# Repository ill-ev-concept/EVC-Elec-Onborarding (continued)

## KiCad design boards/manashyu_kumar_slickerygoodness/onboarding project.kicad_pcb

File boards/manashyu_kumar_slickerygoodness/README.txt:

Lights controller onboarding project
Manashyu Kumar

Open onboarding project.kicad_pro in KiCad 10.
Two-layer board, 85 x 65 mm.

Backpack.pretty and libs contain the custom footprints and symbols.
manufacturing contains the Gerber and separate plated/nonplated drill files.

DRC and schematic parity checks passed on October 12, 2026 using the project's configured rules.
For team review: confirm connector pinouts and fit, LED load current, and power-track capacity before fabrication. CAN and main grounds are separate; isolation performance has not been validated.

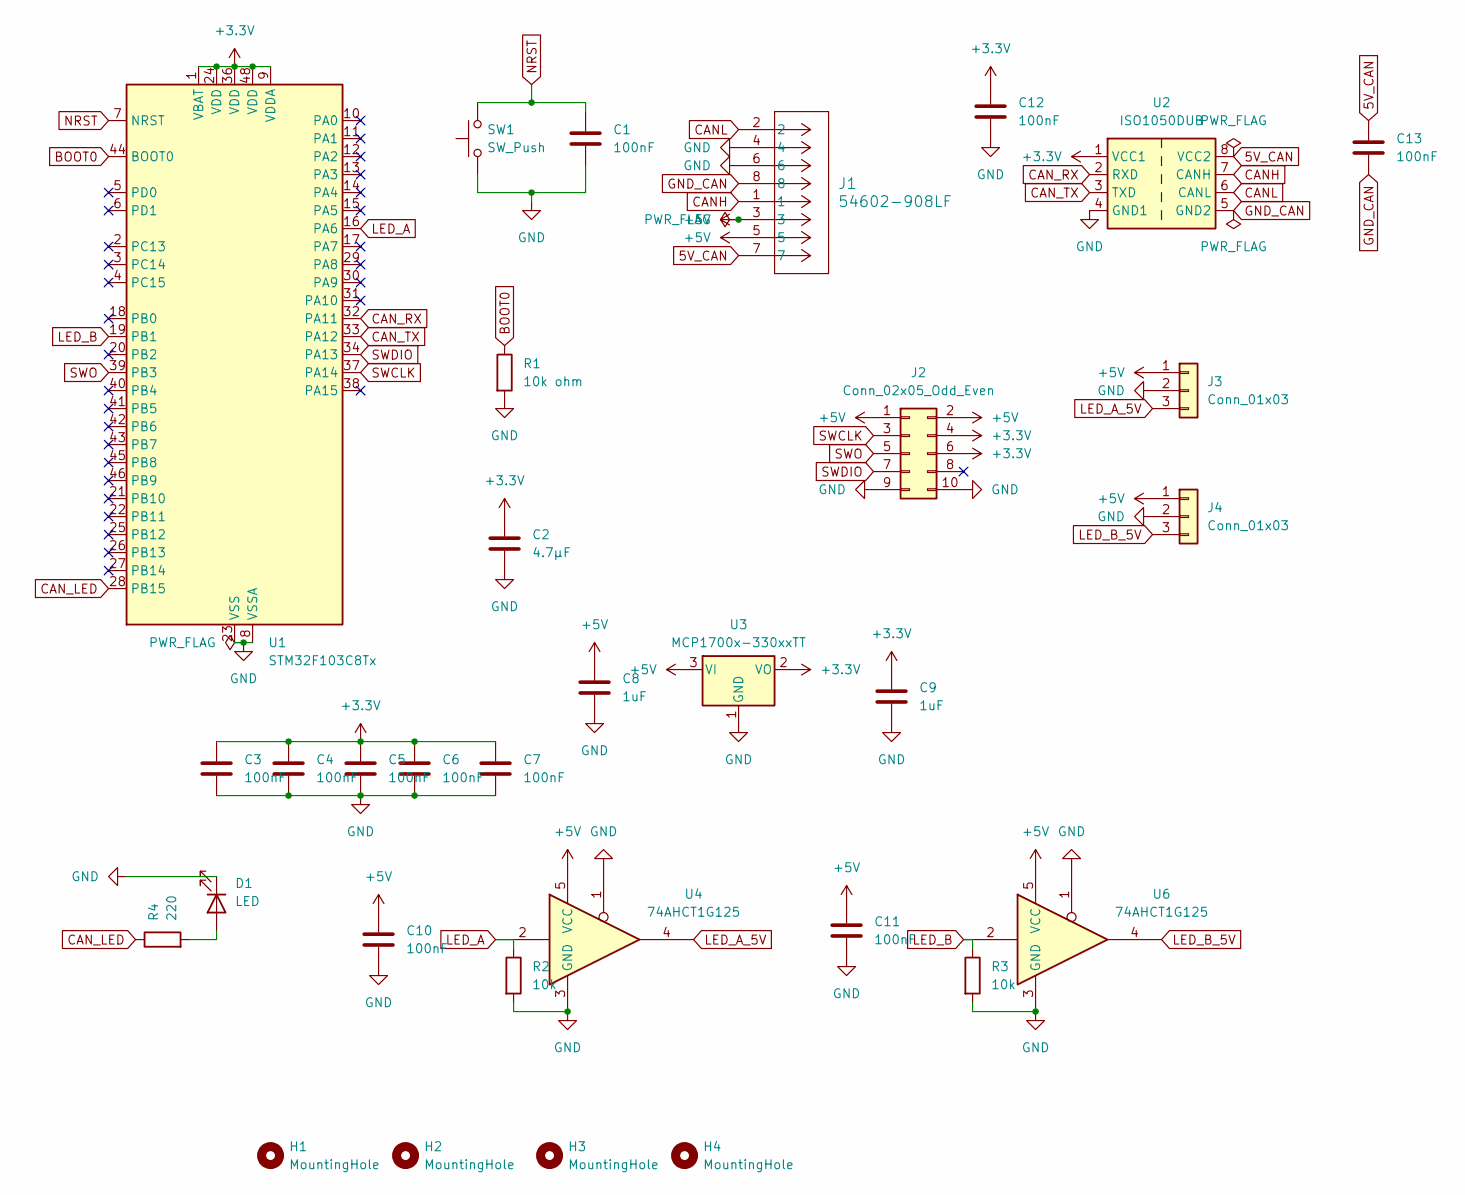
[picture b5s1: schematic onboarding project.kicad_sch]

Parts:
C1, C3, C4, C5, C6, C7, C10, C11, C12, C13: 100nF; C_0805_2012Metric
C2: 4.7µF; C_0805_2012Metric
C8, C9: 1uF; C_0805_2012Metric
D1: LED; LED_0805_2012Metric
H1, H2, H3, H4: MountingHole; MountingHole_4.3mm_M4
J1: 54602-908LF; AMPHENOL_54602-908LF
J2: Conn_02x05_Odd_Even; PinSocket_2x05_P2.54mm_Vertical
J3, J4: Conn_01x03; CONN_2157600003-SD_03_PEG_MOL
R1: 10k ohm; R_0805_2012Metric
R2, R3: 10k; R_0805_2012Metric
R4: 220; R_0805_2012Metric
SW1: SW_Push; SW_PUSH_6mm
U1: STM32F103C8Tx; LQFP-48_7x7mm_P0.5mm
U2: ISO1050DUB; SOP254P1040X485-8N
U3: MCP1700x-330xxTT; SOT-23
U4, U6: 74AHCT1G125; SOT-23-5

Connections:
5V_CAN: C13.1, J1.7, U2.8 (VCC2)
+3.3V: C2.1, C3.1, C4.1, C5.1, C6.1, C7.1, C9.1, C12.1, J2.4, J2.6, U1.1 (VBAT), U1.9 (VDDA), U1.24 (VDD), U1.36 (VDD), U1.48 (VDD), U2.1 (VCC1), U3.2 (VO)
+5V: C8.1, C10.1, C11.1, J1.3, J1.5, J2.1, J2.2, J3.1, J4.1, U3.3 (VI), U4.5 (VCC), U6.5 (VCC)
BOOT0: R1.1, U1.44 (BOOT0)
CANH: J1.1, U2.7 (CANH)
CANL: J1.2, U2.6 (CANL)
CAN_LED: R4.1, U1.28 (PB15)
CAN_RX: U1.32 (PA11), U2.2 (RXD)
CAN_TX: U1.33 (PA12), U2.3 (TXD)
GND: C1.2, C2.2, C3.2, C4.2, C5.2, C6.2, C7.2, C8.2, C9.2, C10.2, C11.2, C12.2, D1.1 (K), J1.4, J1.6, J2.9, J2.10, J3.2, J4.2, R1.2, R2.2, R3.2, SW1.1, U1.8 (VSSA), U1.23 (VSS), U1.35 (VSS), U1.47 (VSS), U2.4 (GND1), U3.1 (GND), U4.1, U4.3 (GND), U6.1, U6.3 (GND)
GND_CAN: C13.2, J1.8, U2.5 (GND2)
LED_A: R2.1, U1.16 (PA6), U4.2
LED_A_5V: J3.3, U4.4
LED_B: R3.1, U1.19 (PB1), U6.2
LED_B_5V: J4.3, U6.4
NRST: C1.1, SW1.2, U1.7 (NRST)
unnamed: D1.2 (A), R4.2
SWCLK: J2.3, U1.37 (PA14)
SWDIO: J2.7, U1.34 (PA13)
SWO: J2.5, U1.39 (PB3)

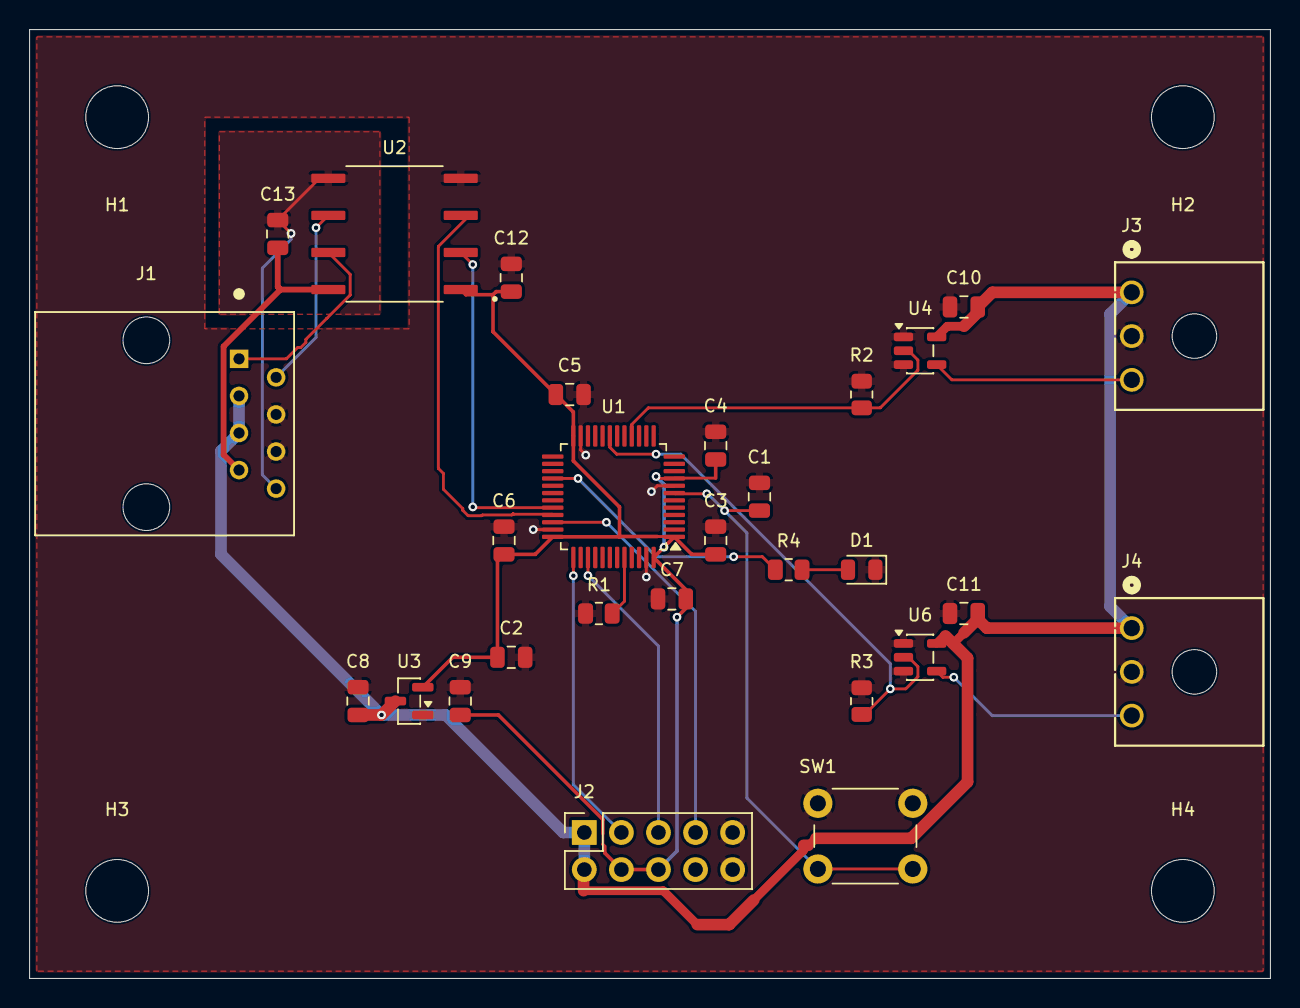
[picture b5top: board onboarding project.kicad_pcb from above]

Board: 2 copper layers, 85.0 x 65.0 mm, 32 parts (0 on the bottom side), 20 nets.

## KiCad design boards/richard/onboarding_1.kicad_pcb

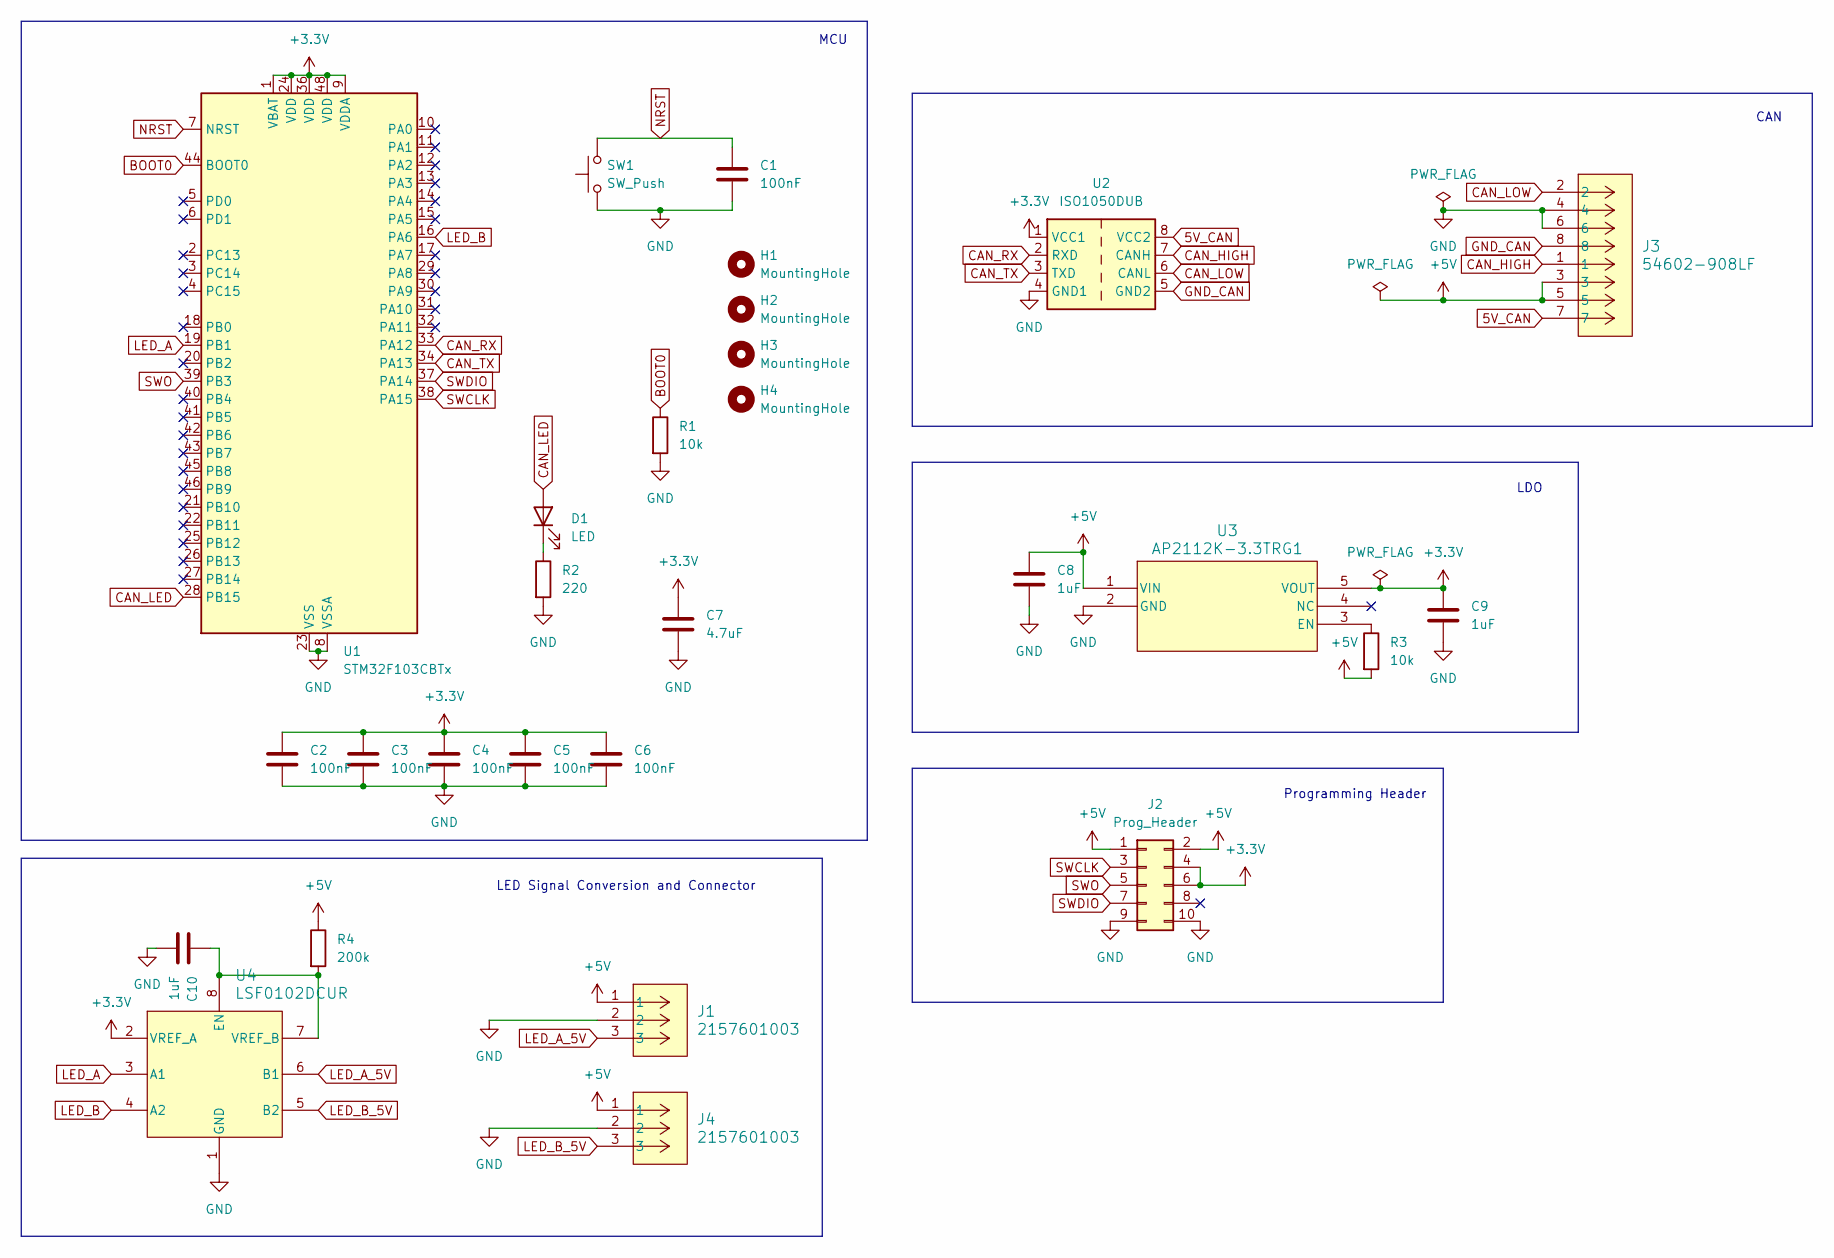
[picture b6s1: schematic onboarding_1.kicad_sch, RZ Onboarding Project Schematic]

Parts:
C1, C2, C3, C4, C5, C6: 100nF; C_0805_2012Metric
C7: 4.7uF; C_0805_2012Metric
C8, C9, C10: 1uF; C_0805_2012Metric
D1: LED; LED_0805_2012Metric
H1, H2, H3, H4: MountingHole; MountingHole_3.2mm_M3
J1, J4: 2157601003; CONN_2157600003-SD_03_PEG_MOL
J2: Prog_Header; PinSocket_2x05_P2.54mm_Vertical
J3: 54602-908LF; CONN8_2-908LF_AMP
R1, R3: 10k; R_0805_2012Metric
R2: 220; R_0805_2012Metric
R4: 200k; R_0805_2012Metric
SW1: SW_Push; SW_SPST_EVQQ2
U1: STM32F103CBTx; LQFP-48_7x7mm_P0.5mm
U2: ISO1050DUB; SOP-8_6.62x9.15mm_P2.54mm
U3: AP2112K-3.3TRG1; SOT_RG1_DIO
U4: LSF0102DCUR; DCU0008A_N

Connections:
5V_CAN: J3.7, U2.8 (VCC2)
+3.3V: C2.1, C3.1, C4.1, C5.1, C6.1, C7.1, C9.1, J2.4, J2.6, U1.1 (VBAT), U1.9 (VDDA), U1.24 (VDD), U1.36 (VDD), U1.48 (VDD), U2.1 (VCC1), U3.5 (VOUT), U4.2 (VREF_A)
+5V: C8.1, J1.1, J2.1, J2.2, J3.3, J3.5, J4.1, R3.2, R4.1, U3.1 (VIN)
BOOT0: R1.1, U1.44 (BOOT0)
CAN_HIGH: J3.1, U2.7 (CANH)
CAN_LED: D1.2 (A), U1.28 (PB15)
CAN_LOW: J3.2, U2.6 (CANL)
CAN_RX: U1.33 (PA12), U2.2 (RXD)
CAN_TX: U1.34 (PA13), U2.3 (TXD)
GND: C1.2, C2.2, C3.2, C4.2, C5.2, C6.2, C7.2, C8.2, C9.2, C10.2, J1.2, J2.9, J2.10, J3.4, J3.6, J4.2, R1.2, R2.2, SW1.1, U1.8 (VSSA), U1.23 (VSS), U1.35 (VSS), U1.47 (VSS), U2.4 (GND1), U3.2 (GND), U4.1 (GND)
GND_CAN: J3.8, U2.5 (GND2)
LED_A: U1.19 (PB1), U4.3 (A1)
LED_A_5V: J1.3, U4.6 (B1)
LED_B: U1.16 (PA6), U4.4 (A2)
LED_B_5V: J4.3, U4.5 (B2)
NRST: C1.1, SW1.2, U1.7 (NRST)
unnamed: D1.1 (K), R2.1
unnamed: R3.1, U3.3 (EN)
unnamed: C10.1, R4.2, U4.7 (VREF_B), U4.8 (EN)
SWCLK: J2.3, U1.38 (PA15)
SWDIO: J2.7, U1.37 (PA14)
SWO: J2.5, U1.39 (PB3)

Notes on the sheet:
LED Signal Conversion and Connector
CAN
Programming Header
MCU
LDO

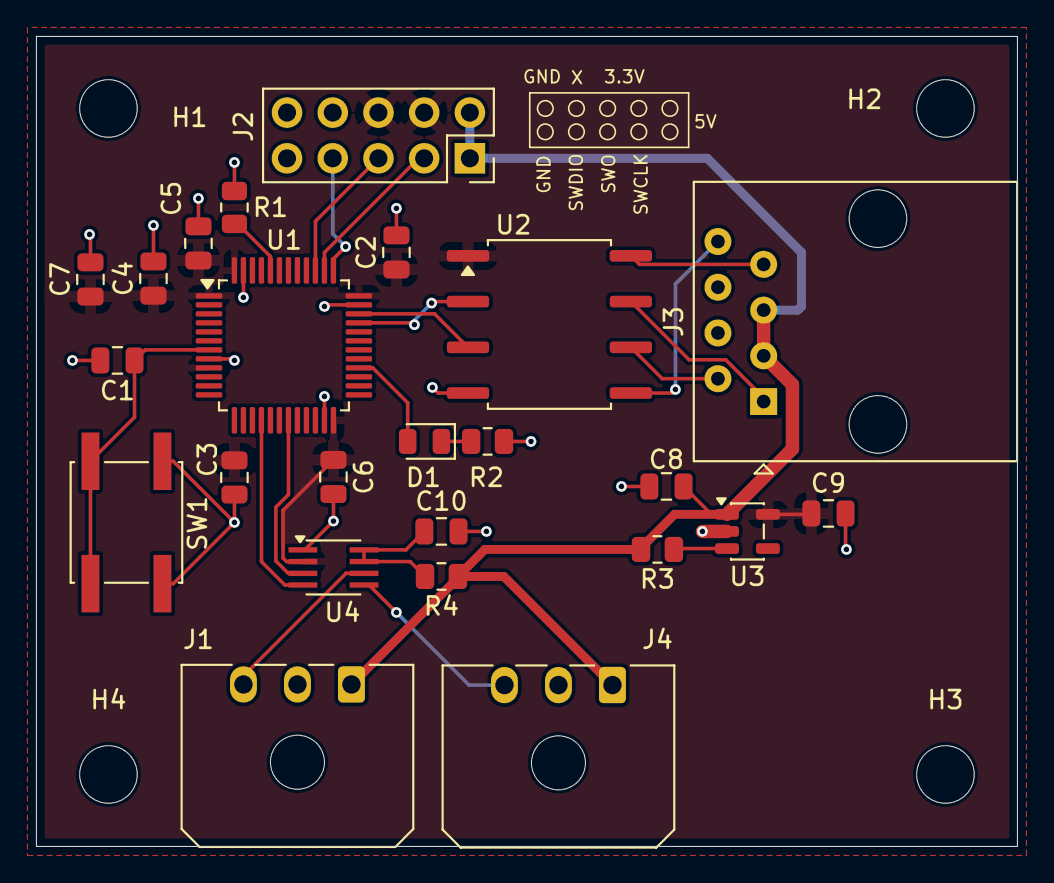
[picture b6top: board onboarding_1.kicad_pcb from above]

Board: 2 copper layers, 54.5 x 45.0 mm, 28 parts (0 on the bottom side), 22 nets.
